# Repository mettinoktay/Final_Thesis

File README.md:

# Final_Thesis

Is anyone reading this? Okay.

Here is the bachelor thesis work of mine at Yıldız Technical University in İstanbul. I'm building a small scale wind turbine.

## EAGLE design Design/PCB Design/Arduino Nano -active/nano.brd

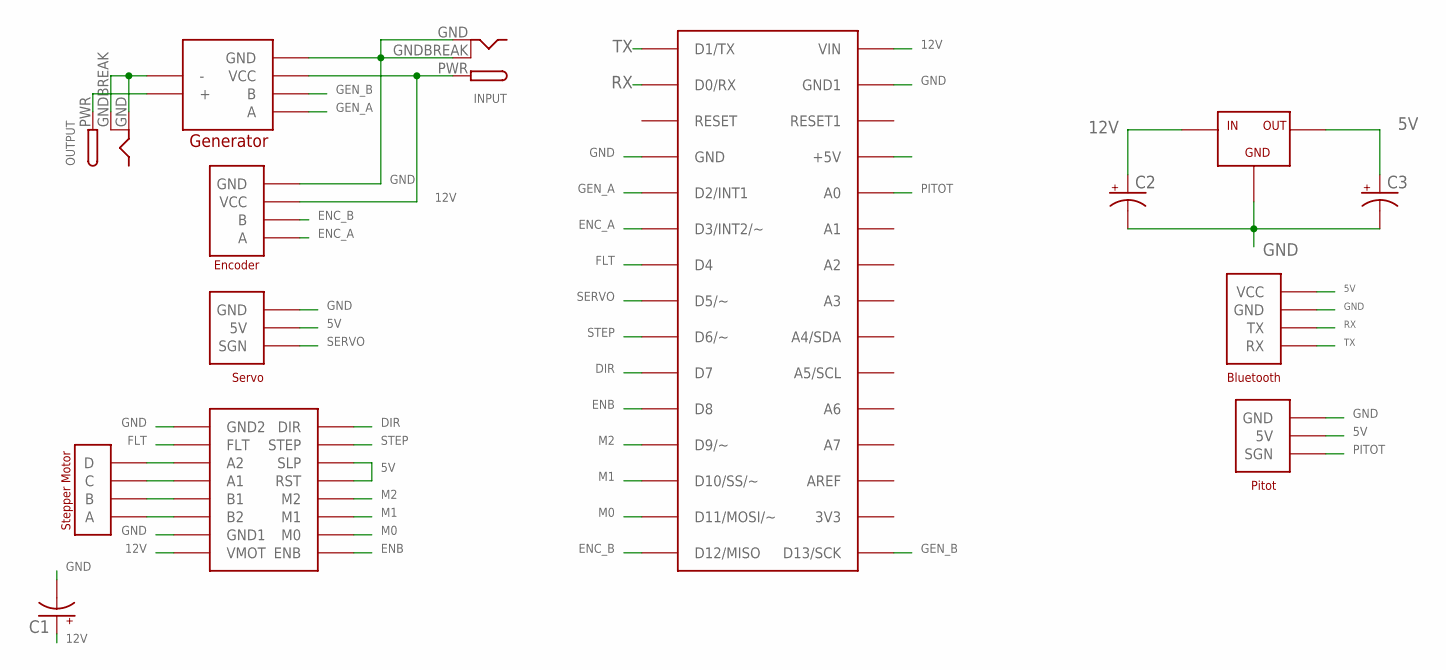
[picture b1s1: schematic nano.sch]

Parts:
C1, C2, C3: 100UF-25V-20%(PTH); CPOL-RADIAL-100UF-25V
INPUT: DCBARRELPTH; DCJACK_2MM_PTH
NANO: ARDUINONANO; PDIP-32
OUTPUT: DCBARRELPTH; DCJACK_2MM_PTH
U$1: HC06
U$2: ENCODER
U$3: PITOT
U$4: STEPPER
U$5: STEPPER_DRIVER
U$6: SERVO
U$7: GENERATOR
U$8: 7805

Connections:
5V: C3.1 (+), NANO.+5V, U$1.VCC, U$3.5V, U$5.RST, U$5.SLP, U$6.5V, U$8.OUT
12V: C1.1 (+), C2.1 (+), INPUT.PWR, NANO.VIN, U$2.VCC, U$5.VMOT, U$7.VCC, U$8.IN
DIR: NANO.D7, U$5.DIR
ENB: NANO.D8, U$5.ENB
ENC_A: NANO.D3 (D3/INT2/~), U$2.A
ENC_B: NANO.D12 (D12/MISO), U$2.B
FLT: NANO.D4, U$5.FLT
GEN_A: NANO.D2 (D2/INT1), U$7.A
GEN_B: NANO.D13 (D13/SCK), U$7.B
GND: C1.2 (-), C2.2 (-), C3.2 (-), INPUT.GND, INPUT.GNDBREAK, NANO.GND, NANO.GND1, OUTPUT.GND, OUTPUT.GNDBREAK, U$1.GND, U$2.GND, U$3.GND, U$5.GND (GND1), U$5.GND1 (GND2), U$6.GND, U$7.-, U$7.GND, U$8.GND
M0: NANO.D11 (D11/MOSI/~), U$5.M0
M1: NANO.D10 (D10/SS/~), U$5.M1
M2: NANO.D9 (D9/~), U$5.M2
unnamed: U$4.D, U$5.A2
unnamed: U$4.C, U$5.A1
unnamed: U$4.B, U$5.B1
unnamed: U$4.A, U$5.B2
unnamed: OUTPUT.PWR, U$7.+
PITOT: NANO.A0, U$3.SGN
RX: NANO.D0/RX, U$1.TX
SERVO: NANO.D5 (D5/~), U$6.SGN
STEP: NANO.D6 (D6/~), U$5.STEP
TX: NANO.D1/TX, U$1.RX

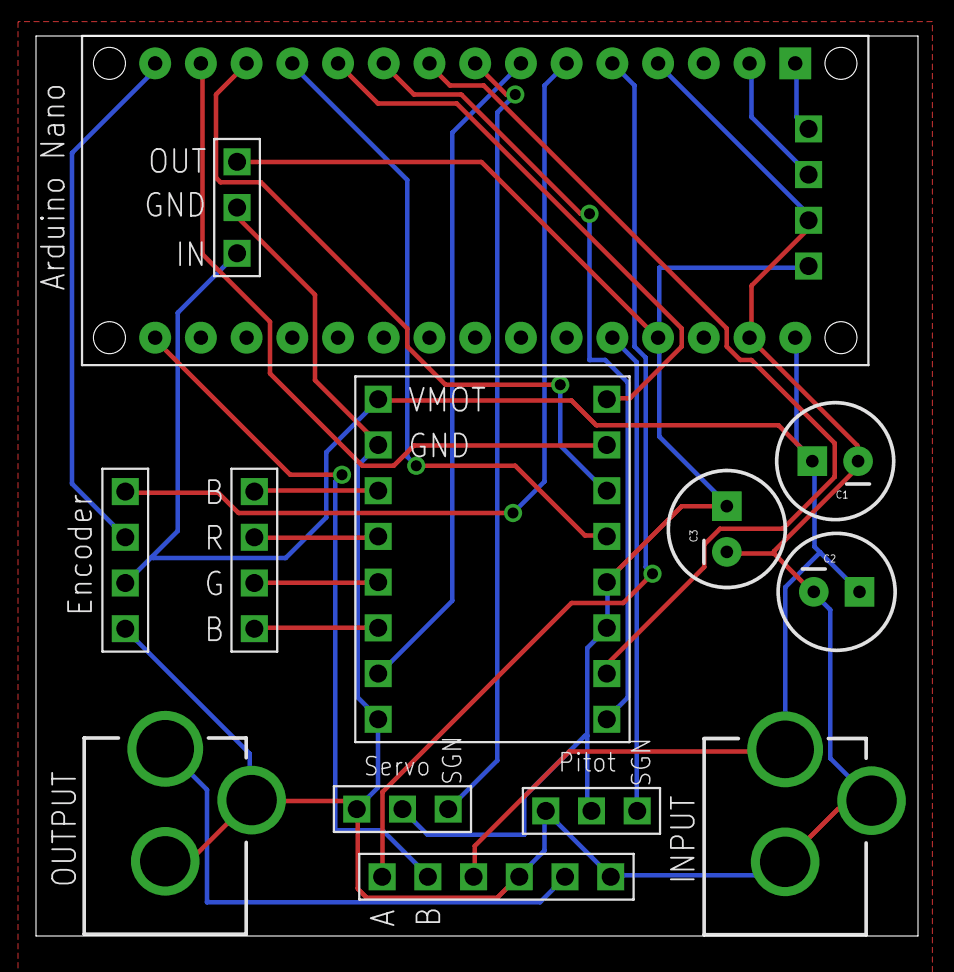
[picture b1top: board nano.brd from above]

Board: 2 copper layers, 49.0 x 50.0 mm, 14 parts (1 on the bottom side), 23 nets.

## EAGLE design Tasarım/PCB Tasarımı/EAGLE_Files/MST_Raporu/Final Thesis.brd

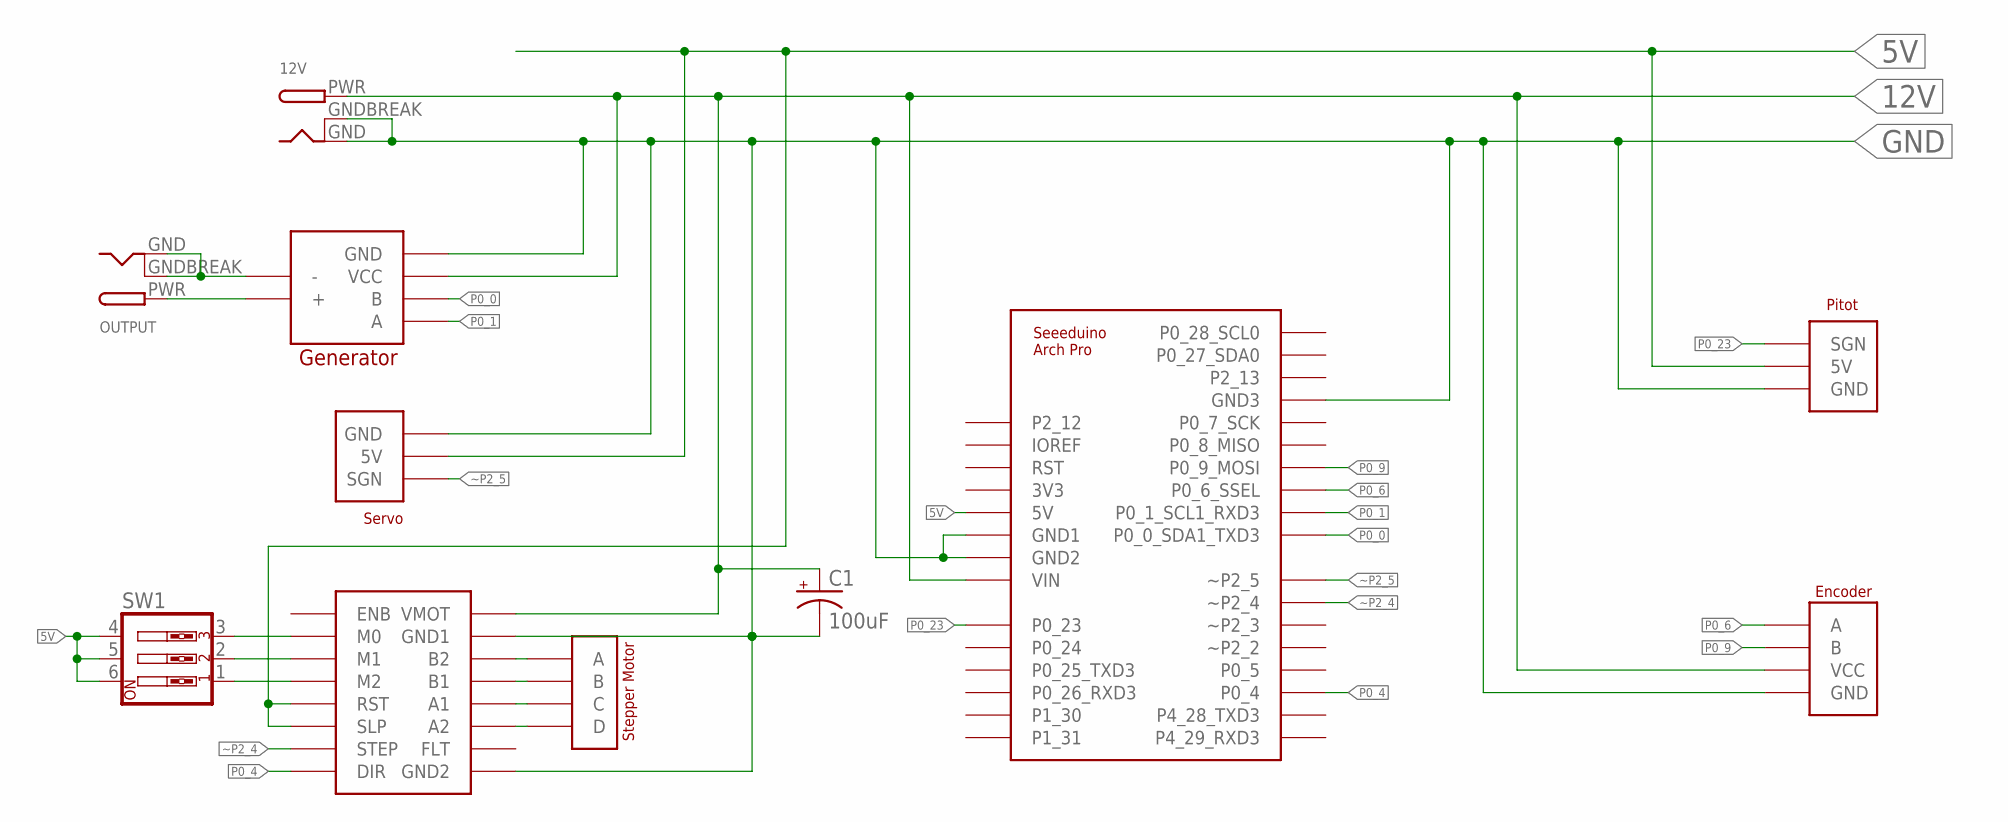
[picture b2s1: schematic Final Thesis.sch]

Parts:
12V: DCBARRELPTH; DCJACK_2MM_PTH
C1: 100uF; CPOL-RADIAL-100UF-25V
OUTPUT: DCBARRELPTH; DCJACK_2MM_PTH
SAP1: ARCH_PROSHIELD; ARCH_PRO
SW1: SW_DIP-3; EDG-03
U$1: ENCODER
U$2: GENERATOR
U$3: PITOT
U$4: SERVO
U$5: STEPPER
U$6: STEPPER_DRIVER

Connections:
5V: SAP1.5V, SW1.4, SW1.5, SW1.6, U$3.5V, U$4.5V, U$6.RST, U$6.SLP
12V: 12V.PWR, C1.1 (+), SAP1.VIN, U$1.VCC, U$2.VCC, U$6.VMOT
GND: 12V.GND, 12V.GNDBREAK, C1.2 (-), SAP1.GND1, SAP1.GND2, SAP1.GND3, U$1.GND, U$2.GND, U$3.GND, U$4.GND, U$6.GND (GND1), U$6.GND1 (GND2)
unnamed: U$5.A, U$6.B2
unnamed: U$5.B, U$6.B1
unnamed: U$5.C, U$6.A1
unnamed: U$5.D, U$6.A2
unnamed: OUTPUT.PWR, U$2.+
unnamed: SW1.3, U$6.M0
unnamed: SW1.2, U$6.M1
unnamed: SW1.1, U$6.M2
unnamed: OUTPUT.GND, OUTPUT.GNDBREAK, U$2.-
P0_0: SAP1.P0_0_SDA1_TXD3, U$2.B
P0_1: SAP1.P0_1_SCL1_RXD3, U$2.A
P0_4: SAP1.P0_4, U$6.DIR
P0_6: SAP1.P0_6_SSEL, U$1.A
P0_9: SAP1.P0_9_MOSI, U$1.B
P0_23: SAP1.P0_23, U$3.SGN
~P2_4: SAP1.~P2_4, U$6.STEP
~P2_5: SAP1.~P2_5, U$4.SGN

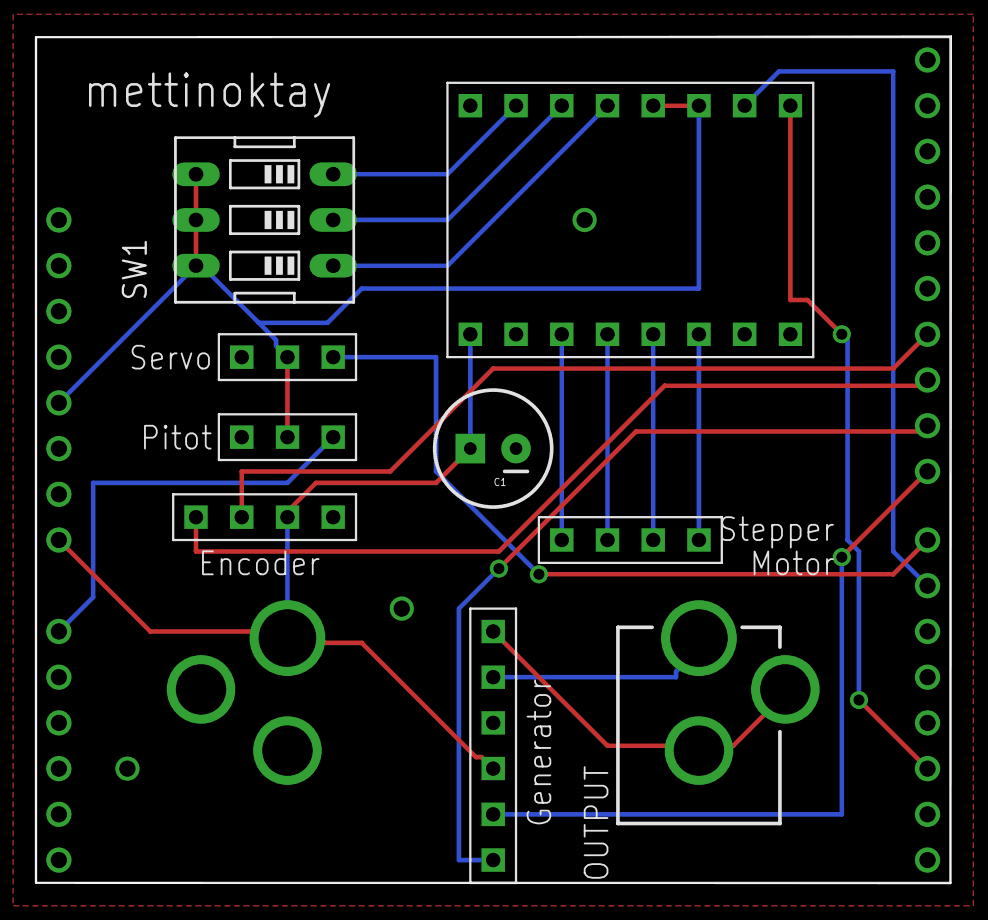
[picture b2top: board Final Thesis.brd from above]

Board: 2 copper layers, 50.9 x 47.1 mm, 11 parts (1 on the bottom side), 20 nets.

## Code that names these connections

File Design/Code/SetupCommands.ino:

void setupSystem(){
 // put your setup code here, to run once:
  Serial.begin(9600);
  Serial.flush();
  pinMode(M2, OUTPUT);
  pinMode(M1, OUTPUT);
  pinMode(M0, OUTPUT);
  pinMode(FLT, INPUT);
  pinMode(ENB, OUTPUT);
  pinMode(STEP, OUTPUT);
  pinMode(DIR, OUTPUT);
  pinMode(SERVO, OUTPUT);
  pinMode(GEN_B, INPUT);
  pinMode(ENC_B, INPUT);
//attachInterrupt(digitalPinToInterrupt(ENC_A), wind, RISING);
//attachInterrupt(digitalPinToInterrupt(GEN_A), ISR, RISING);
  pitchServo.attach(SERVO);  
  disableStepper();
  //enableStepper();
  microStepping(FULL);
}

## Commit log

2016-02-01 :confetti_ball: Added .gitattributes & .gitignore files
2016-02-01 Added design files and reports
    Final report, PCB files and blade design .m file has been uploaded.
2016-02-01 Added EAGLE Files
    EAGLE files of custom shield for controller
2016-03-05 First Version
2016-03-05 Translated names
    Folder and file names translated to English
2016-03-05 Changed readme completely
2016-03-05 Seperated component's functions
2016-03-05 Created seperate .ino files for each element's functions
2016-03-06 Deleted unnecessary files, added EAGLE files of new design
2016-03-11 Updated PitotFunctions.ino
2016-03-24 Switched to PlatformIO
2016-06-03 Too many changes
    Made too many changes to remember.
2016-07-19 Changed library directories
2016-07-22 Minor update
2016-11-15 Minor Change

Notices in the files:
parts and their libraries:
SparkFun-Capacitors: Licensing: Creative Commons ShareAlike 4.0 International - https://creativecommons.org/licenses/by-sa/4.0
